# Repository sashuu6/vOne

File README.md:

# vOne

## Introduction

My version of Arduino Uno for board isolation.

Design Tool : Autodesk Eagle PCB

## Front Design

## Bottom Design

## Drills Design

## Features

1. 5 5V pins
2. 5 3.3V pins
3. 10 ground pins
4. Extra filtering input from power source
5. FTDI support
6. Supports 9V AC and DC

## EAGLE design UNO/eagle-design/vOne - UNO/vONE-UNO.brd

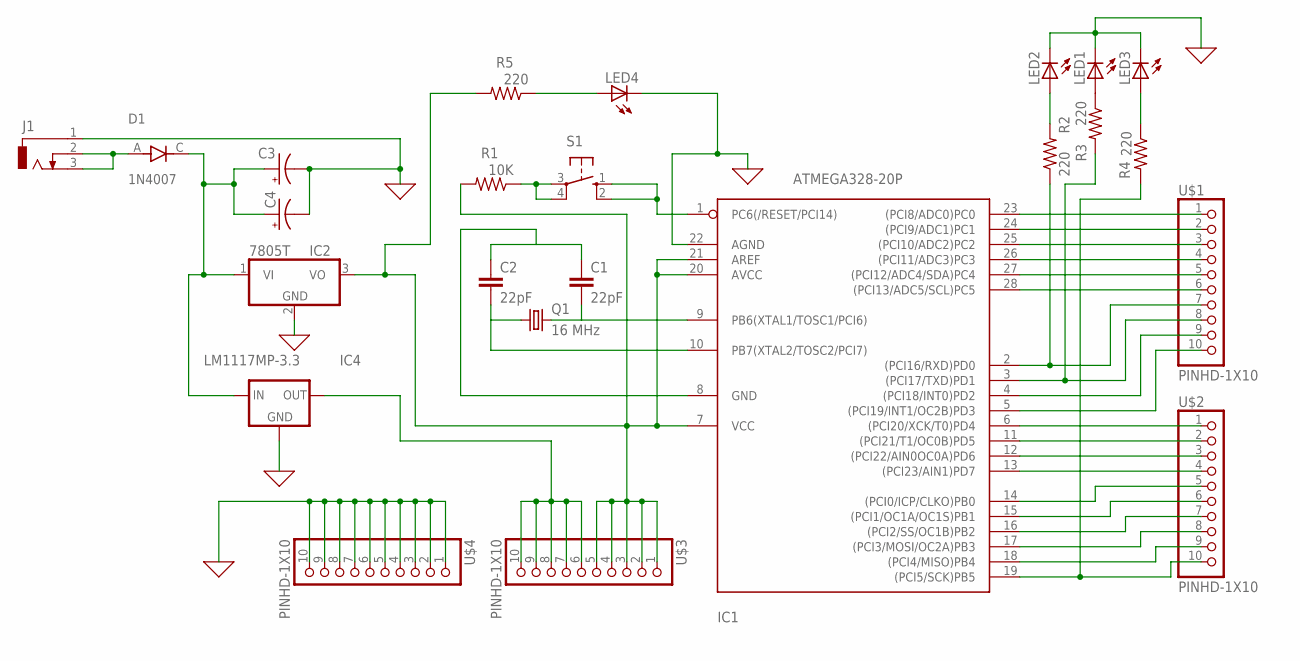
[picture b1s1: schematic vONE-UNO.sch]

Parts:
C1, C2: 22pF; C2.5-3
C3, C4: CPOL-USE2,5-6E; E2,5-6E
D1: 1N4007; DIOAD1060W80L520D270
IC1: ATMEGA328-20P; DIL28-3
IC2: 7805T; TO220H
IC4: LM1117MP-3.3; SOT223
J1: DCJ0303
LED1, LED2, LED3, LED4: LED5MM
Q1: 16 MHz; HC49/S
R1: 10K; 0805-THM
R2, R3, R4, R5: 220; 0805-THM
S1: 10-XX; B3F-10XX
U$1, U$2, U$3, U$4: PINHD-1X10; 1X10-BIG

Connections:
0: C3.-, C4.-, IC1.22 (AGND), IC2.2 (GND), IC4.1 (GND), J1.1, LED1.K (C), LED2.K (C), LED3.K (C), LED4.K (C), U$4.1, U$4.2, U$4.3, U$4.4, U$4.5, U$4.6, U$4.7, U$4.8, U$4.9, U$4.10
unnamed: D1.A, J1.2, J1.3
unnamed: IC1.1 (PC6(/RESET/PCI14)), S1.1 (S), S1.2 (S1)
unnamed: C1.1, C2.1, IC1.8 (GND)
unnamed: IC1.23 ((PCI8/ADC0)PC0), U$1.1
unnamed: IC1.24 ((PCI9/ADC1)PC1), U$1.2
unnamed: IC1.25 ((PCI10/ADC2)PC2), U$1.3
unnamed: IC1.26 ((PCI11/ADC3)PC3), U$1.4
unnamed: IC1.27 ((PCI12/ADC4/SDA)PC4), U$1.5
unnamed: IC1.28 ((PCI13/ADC5/SCL)PC5), U$1.6
unnamed: IC1.2 ((PCI16/RXD)PD0), R3.1, U$1.7
unnamed: R1.1, S1.3, S1.4 (P1)
unnamed: C1.2, IC1.9 (PB6(XTAL1/TOSC1/PCI6)), Q1.2
unnamed: C2.2, IC1.10 (PB7(XTAL2/TOSC2/PCI7)), Q1.1
unnamed: IC1.4 ((PCI18/INT0)PD2), U$1.9
unnamed: IC1.5 ((PCI19/INT1/OC2B)PD3), U$1.10
unnamed: IC1.19 ((PCI5/SCK)PB5), R4.2, U$2.10
unnamed: IC1.11 ((PCI21/T1/OC0B)PD5), U$2.2
unnamed: IC1.12 ((PCI22/AIN0OC0A)PD6), U$2.3
unnamed: IC1.13 ((PCI23/AIN1)PD7), U$2.4
unnamed: IC1.14 ((PCI0/ICP/CLKO)PB0), U$2.5
unnamed: IC1.15 ((PCI1/OC1A/OC1S)PB1), U$2.6
unnamed: IC1.16 ((PCI2/SS/OC1B)PB2), U$2.7
unnamed: IC1.17 ((PCI3/MOSI/OC2A)PB3), U$2.8
unnamed: IC1.18 ((PCI4/MISO)PB4), U$2.9
unnamed: LED4.A, R5.1
unnamed: IC4.2 (OUT), IC4.4 (OUT), U$3.6, U$3.7, U$3.8, U$3.9, U$3.10
unnamed: LED2.A, R3.2
unnamed: LED1.A, R2.1
unnamed: LED3.A, R4.1
unnamed: IC1.7 (VCC), IC1.20 (AVCC), IC1.21 (AREF), IC2.3 (VO), R1.2, R5.2, U$3.1, U$3.2, U$3.3, U$3.4, U$3.5
unnamed: C3.+, C4.+, D1.C, IC2.1 (VI), IC4.3 (IN)
unnamed: IC1.6 ((PCI20/XCK/T0)PD4), U$2.1
unnamed: IC1.3 ((PCI17/TXD)PD1), R2.2, U$1.8

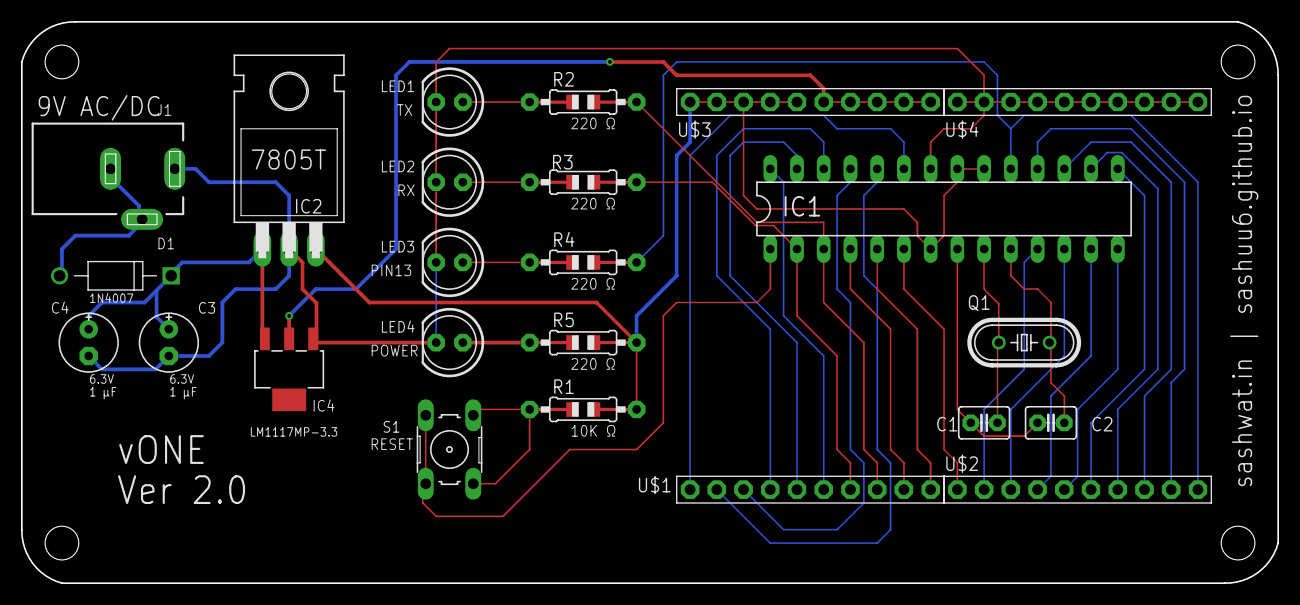
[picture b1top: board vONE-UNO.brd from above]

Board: 2 copper layers, 119.4 x 53.3 mm, 24 parts (0 on the bottom side), 34 nets.

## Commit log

2019-03-26 prototype - 1
2019-04-07 working on documentation
2019-04-07 completed documentation
2019-04-07 small change
2019-08-08 gerber file
2019-11-11 Added bendpoints and now its version 2
2019-11-11 version 2 documentation
2019-11-11 Added gerber file
2020-09-27 Added LM1117 3.3V regulator support
2020-09-27 Removed fritzing design
2020-09-27 Added Eagle design and Atmel datasheet
2020-09-28 Added eagle library
2020-10-10 Board design
2020-10-10 removed old
2020-10-10 Added new board
2020-10-11 Removed old design
2020-10-11 Added new design
2020-10-11 Final design complete
2020-10-11 Added documentation for new design
2021-06-13 Fixed documentation error
2021-06-13 Fixed image link error
2021-06-13 Doc error
2021-06-13 Fixed schematics error
2021-06-13 Added intermediate files
2021-06-13 Fixed design error
2021-06-13 eagle update
2021-07-17 Updated design
2021-07-17 Doc reorg
2021-07-17 Bug fix
